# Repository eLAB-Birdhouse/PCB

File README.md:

This repository contains the design file of the POE hat required for this project.

The design is highly inspired from the following product: https://www.waveshare.com/wiki/ETH/USB_HUB_HAT

A template for the has been used for the hat (it is under a MIT license): https://github.com/rkprojects/kicad-rpiz-uhat-template

Another useful ressource for hat in general is : https://github.com/raspberrypi/hats/blob/master/designguide.md

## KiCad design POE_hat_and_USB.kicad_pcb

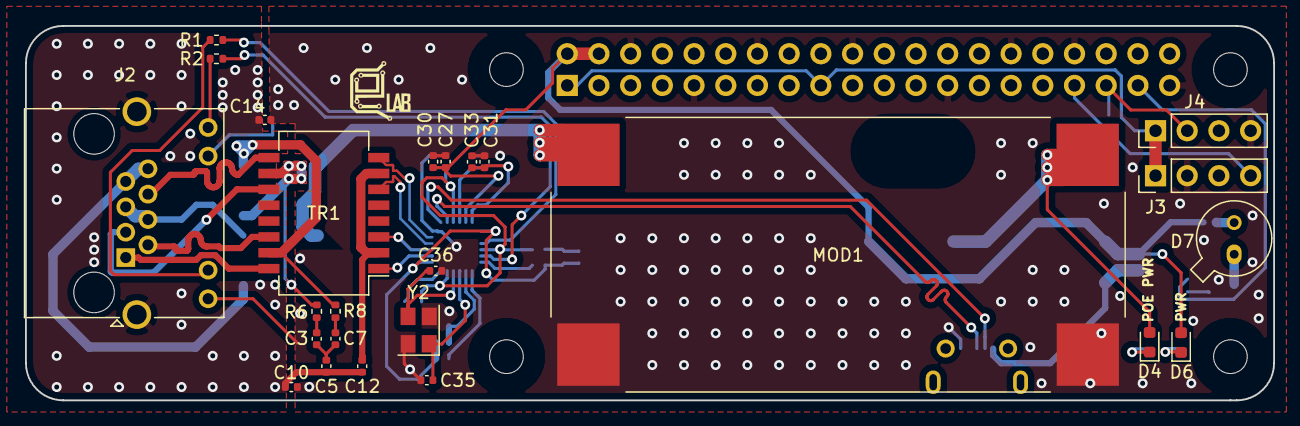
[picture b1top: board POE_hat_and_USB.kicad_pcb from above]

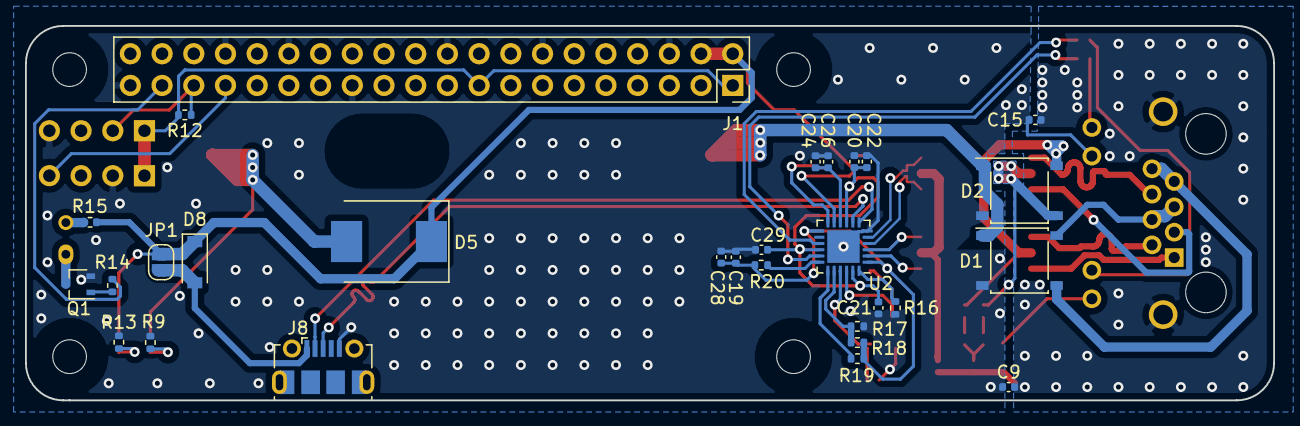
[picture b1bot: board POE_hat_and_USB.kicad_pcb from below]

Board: 2 copper layers, 100.0 x 30.0 mm, 58 parts (29 on the bottom side), 47 nets.

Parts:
C3, C7: 10 nF - 100 V; C_0402_1005Metric
C5: 1000; C_0402_1005Metric
C9, C10, C14, C15, C19, C21, C22, C26, C28, C29, C30, C33: 0.1; C_0402_1005Metric
C12: 10; C_0402_1005Metric
C20, C24, C27: 4.7; C_0402_1005Metric
C31: 1; C_0402_1005Metric
C35, C36: 14; C_0402_1005Metric
D1, D2: ABS10; Diode_Bridge_Diotec_ABS
D4: POE_PWR; LED_0603_1608Metric
D5: B560C; D_SMC
D6: PWR; LED_0603_1608Metric
D7: OP293B; TO-46-2
D8: MBR0520LT1G; D_SOD-123
H1, H2, H3, H4: MountingHole; MountingHole_2.7mm_M2.5_uHAT_RPi
J1: GPIO_CONNECTOR; PinSocket_2x20_P2.54mm_Vertical_Centered_Anchor
J2: RJHSE-5385; RJ45_Amphenol_RJHSE538X
J3: PIR Motion Sensor; PinHeader_1x04_P2.54mm_Vertical
J4: DH22T; PinHeader_1x04_P2.54mm_Vertical
J8: USB_B_Micro; USB_Micro-B_Molex-105017-0001
JP1: Jumper_NO_Small; SolderJumper-2_P1.3mm_Open_RoundedPad1.0x1.5mm
MOD1: LM2596HVS; Module_LM2596HVS
Q1: DMG1012UW-7; SOT-323_SC-70
R1, R2: 680; R_0402_1005Metric
R6, R8: 75; R_0402_1005Metric
R9, R13: 2.7k; R_0402_1005Metric
R12, R14, R17, R18, R19, R20: 12k; R_0402_1005Metric
R15: 1k; R_0402_1005Metric
R16: 2.49k 1%; R_0402_1005Metric
TR1: PT61017PEL; Transformer_Ethernet_Bourns_PT61017PEL
U2: RTL8152B-VB; QFN-24-1EP_4x4mm_P0.5mm_EP2.6x2.6mm
Y2: 25 MHz 30ppm (HELE(Harmony Elec) X3S025000FC1H-HV); Crystal_SMD_3225-4Pin_3.2x2.5mm

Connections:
+3.3VP: J1.1, J1.17, J3.1, J4.1, R12.2
+5V: C27.1, C30.1, D5.1, D6.2, D8.1, J1.2, J1.4, JP1.1, R15.1, U2.11
+VDC: D1.1, D2.1, MOD1.2
/GPIO13: J1.33, J3.4
/GPIO19: J1.35, J4.2, R12.1
/GPIO26: J1.37, R14.1
/LANWAKEB: R19.2, U2.19
/LED0_SPICSB: R1.1, U2.15
/LED1_SPISCK: R2.1, U2.17
/POE_A+: D2.4, R8.1, TR1.15
/POE_A-: D2.3, R6.1, TR1.10
/POE_B+: D1.4, J2.4, J2.5
/POE_B-: D1.3, J2.7, J2.8
/RD+: TR1.6, U2.4
/RD-: TR1.8, U2.5
/RX+: J2.3, TR1.11
/RX-: J2.6, TR1.9
/SPISDI_XTALDET: R20.2, U2.18
/SPISDO: R17.2, R18.2, U2.20
/TD+: TR1.1, U2.2
/TD-: TR1.3, U2.3
/TX+: J2.1, TR1.16
/TX-: J2.2, TR1.14
/USB2+: J8.3, U2.8
/USB2-: J8.2, U2.7
/VDD10: C20.1, C21.1, C22.1, C29.1, U2.9, U2.16, U2.23
/VDD10_UPS: C31.1, C33.1, U2.12
/VDD33: C19.1, C28.1, R18.1, R19.1, R20.1, U2.1, U2.13
/XTAL1: C35.1, U2.21, Y2.1
/XTAL2: C36.1, U2.22, Y2.3
Earth: C5.2, C9.1, C10.1, C12.2, C14.1, C15.1, J2.SH
GND: C9.2, C10.2, C14.2, C15.2, C19.2, C20.2, C21.2, C22.2, C24.2, C26.2, C27.2, C28.2, C29.2, C30.2, C31.2, C33.2, C35.2, C36.2, D1.2, D2.2, J1.6, J1.9, J1.14, J1.20, J1.25, J1.30, J1.34, J1.39, J2.9, J2.11, J3.2, J4.4, J8.5, MOD1.1, MOD1.3, Q1.2, R9.2, R13.2, R16.1, R17.1, U2.6, U2.25, Y2.2, Y2.4
unnamed: C3.1, R6.2
unnamed: C3.2, C5.1, C7.2
unnamed: C7.1, R8.2
unnamed: C12.1, TR1.2, TR1.7
unnamed: C24.1, C26.1, U2.10
unnamed: D4.1, R9.1
unnamed: D6.1, R13.1
unnamed: D7.1, Q1.3
unnamed: D7.2, R15.2
unnamed: D8.2, J8.1, JP1.2
unnamed: J2.10, R1.2
unnamed: J2.12, R2.2
unnamed: Q1.1, R14.2
unnamed: R16.2, U2.24
VDC: D4.2, D5.2, MOD1.4

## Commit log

2021-08-04 Initial version (not viable).
2021-08-04 Remove power supply and USB hub.
2021-08-05 Create footprint and symbol for the LM2596HVS
2021-08-05 Add LM2596HVS to schematic.
2021-08-05 Clean up project.
2021-08-06 Reroute PCB (removing USB hub, changing power supply and crystal).
2021-08-06 v1.1.0 prerelease.
2021-09-04 Add prod files (JLCPCB).

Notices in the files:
POE_hat_and_USB.kicad_pcb:
This PCB design is licensed under MIT Open Source License.
